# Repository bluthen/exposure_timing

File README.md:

# Exposure Timing

A lot of this project is based off New EXposure Timing Analyser (NEXTA): a GNSS-based precise timer, as presented in the wonderful paper [Reaching sub-millisecond accuracy in stellar
occultations and artificial satellites tracking](https://arxiv.org/abs/2301.06378)[arvix] ([local mirror](./nexta_2301.06378.pdf)) by authors K. Kamiński , C. Weber , A. Marciniak , M. Żołnowski & M. Gędek.

The goals are to design electronics and boards to make this easy to use.

 * PCBs that can be easily assembled, and manufactured that allow for easy LED bar registration (By having Aruco markers for example).
   * This should also make it easy to sell kits for people who do not want to solder or hand wire their own.
 * Software:
   * Binaries available for common desktop OS
   * Can automatically finds LED bar
   * Allow manually register LED bar
   * Decode each rows time
   * Generates timing info, real first exposure time, and time for any row (if rolling shutter camera). Recommends offset to be added to header/metadata. 

*Showing the simple GUI after time analysis has been run. Header delta is what should be added to the time stamp to make it more accurate.*

# License
Please note that individual files in the repository have different licenses. For example the NEXTA microcontroller code is under CC BY-SA 4.0 and the some of the analysis software is under the GNU GPL 3.

# Brief Description

There can be delays, or accuracy issues between when the camera is told to start it's exposure and when it actually does. This can be important for time critical applications. Also of importance is the time difference for each row in CMOS cameras with a rolling shutter.

In particular the timing application originally of interest is imaging fast time critical astronomical events. Such events include, LEO satilite, astroid transits, fast NEOs.

A better introduction is described in the paper listed above.

## Example usage

* Take your camera with a lens on it
* Put electronics (NEXTA) in front of camera, square, well focused.
* Take a intial well lit exposure used for LED bar registartion.
* After NEXTA gets GNSS lock and starts blinking, take short exposures in a dark area.
* Use analysis software to get timing info to see the difference between what is in header/metadata.

# Project contents

* [hardware](./hardware) - This includes 3d printed mount, PCB design files, and arduino firmware
* [nexta_analysis](./nexta_analysis) - Software to try to automatically decode timing images
* [nexta_html_decode_form](./nexta_html_decode_form) - A simple web form to decode the LED pattern into a time.

# Issues

There is a still a lot to do, this project is in it's early stages. Check out the [issue tracker](./issues) and, feel free to contribute.

# Instructional Videos/Purchase complete NEXTA kits

* [https://starsynctrackers.com/store/learn-nexta/](https://starsynctrackers.com/store/learn-nexta/) - Includes Arduino, assembled NEXTA Shield, GPS Moudle, GPS Antenna, Plastic Stand, and Micro USB Cable

# Other Projects

If you are interested in this project, you may be also interested in the following.

* [Project Pluto GNSS astrometry](https://www.projectpluto.com/gps_ast.htm) - Take GNSS satelites going across your frame. Since these positions are well known you can use this to get better timing (Probably up to 0.01s)

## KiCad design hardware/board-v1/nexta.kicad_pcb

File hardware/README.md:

# Exposure Timing Hardware

The goal here is to design PCB and other hardware to make registration and alignment easier for automatic timing analysis.

So far we have:
 * Schematics and PCB design ([KiCad](https://www.kicad.org/) and Gerbers)
 * 3d printed electronics stand ([FreeCad](https://www.freecad.org/) and STL)
 * The firmware (Arduino Sketch) provided by the authors of [Reaching sub-millisecond accuracy in stellar
   occultations and artificial satellites tracking](https://arxiv.org/abs/2301.06378)[arvix] ([local mirror](./nexta_2301.06378.pdf)) by authors K. Kamiński1 , C. Weber2 , A. Marciniak1 , M. Żołnowski3 & M. Gędek.

See the issue tracker for more work to be done.

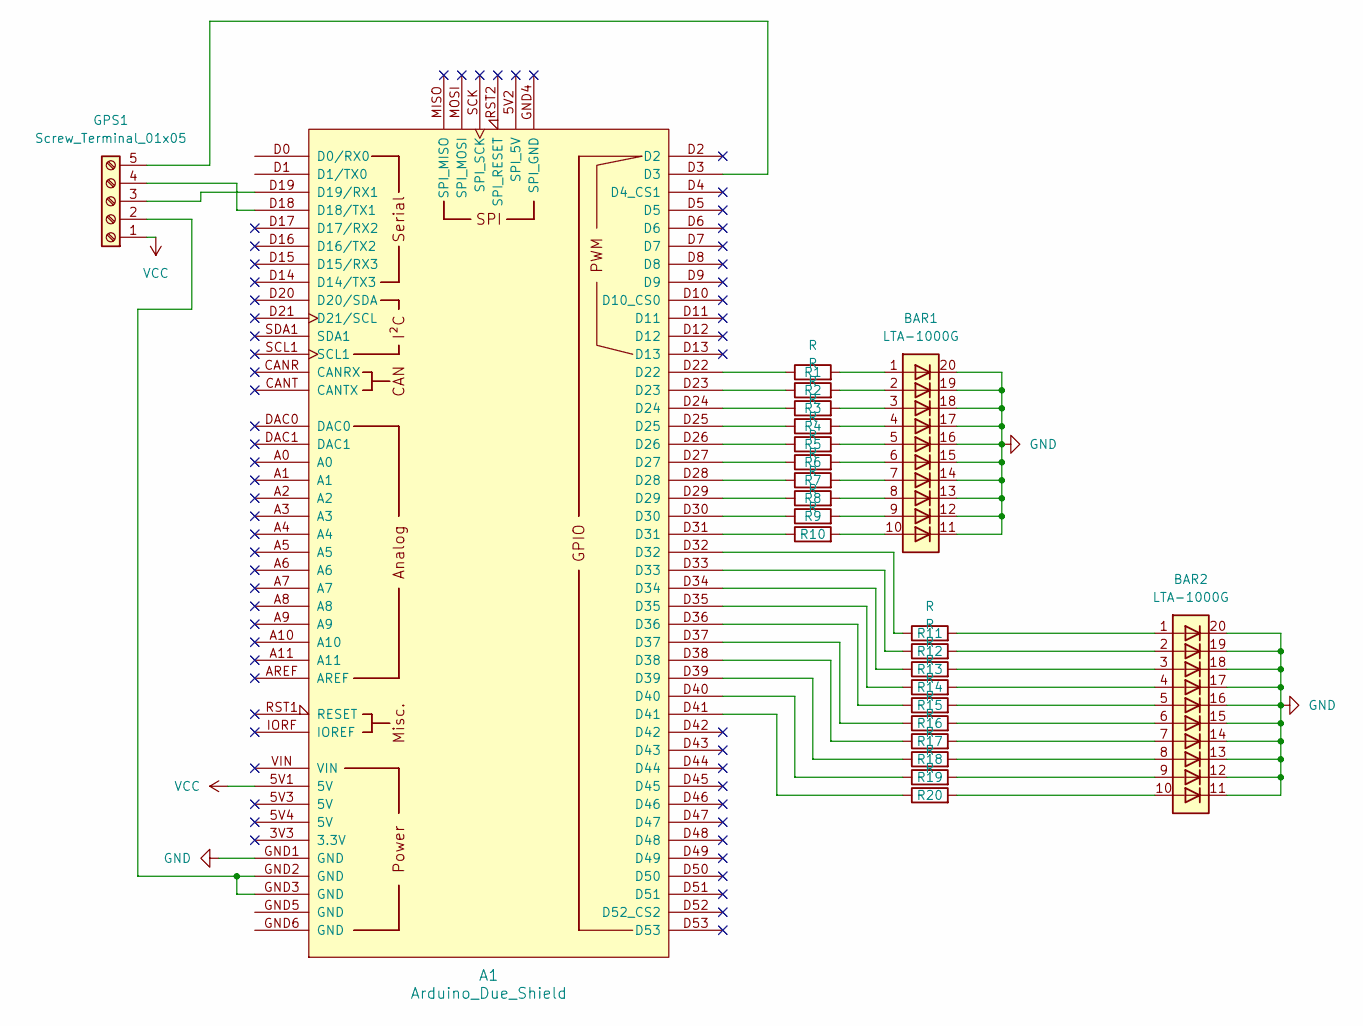
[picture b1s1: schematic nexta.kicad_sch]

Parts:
A1: Arduino_Due_Shield
BAR1, BAR2: LTA-1000G; HDSP-4850
GPS1: Screw_Terminal_01x05; PinHeader_1x05_P2.54mm_Vertical
R1, R2, R3, R4, R5, R6, R7, R8, R9, R10, R11, R12, R13, R14, R15, R16, R17, R18, R19, R20: R; R_0805_2012Metric

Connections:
GND: A1.GND1 (GND), BAR1.11 (K), BAR1.12 (K), BAR1.13 (K), BAR1.14 (K), BAR1.15 (K), BAR1.16 (K), BAR1.17 (K), BAR1.18 (K), BAR1.19 (K), BAR1.20 (K), BAR2.11 (K), BAR2.12 (K), BAR2.13 (K), BAR2.14 (K), BAR2.15 (K), BAR2.16 (K), BAR2.17 (K), BAR2.18 (K), BAR2.19 (K), BAR2.20 (K)
unnamed: A1.D18 (D18/TX1), GPS1.4
unnamed: A1.D19 (D19/RX1), GPS1.3
unnamed: A1.D22, R1.1
unnamed: A1.D23, R2.1
unnamed: A1.D24, R3.1
unnamed: A1.D25, R4.1
unnamed: A1.D26, R5.1
unnamed: A1.D27, R6.1
unnamed: A1.D28, R7.1
unnamed: A1.D29, R8.1
unnamed: A1.D30, R9.1
unnamed: A1.D31, R10.1
unnamed: A1.D32, R11.1
unnamed: A1.D33, R12.1
unnamed: A1.D34, R13.1
unnamed: A1.D35, R14.1
unnamed: A1.D36, R15.1
unnamed: A1.D37, R16.1
unnamed: A1.D38, R17.1
unnamed: A1.D39, R18.1
unnamed: A1.D40, R19.1
unnamed: A1.D41, R20.1
unnamed: BAR1.1 (A), R1.2
unnamed: BAR1.2 (A), R2.2
unnamed: BAR1.3 (A), R3.2
unnamed: BAR1.4 (A), R4.2
unnamed: BAR1.5 (A), R5.2
unnamed: BAR1.6 (A), R6.2
unnamed: BAR1.7 (A), R7.2
unnamed: BAR1.8 (A), R8.2
unnamed: BAR1.9 (A), R9.2
unnamed: BAR1.10 (A), R10.2
unnamed: BAR2.1 (A), R11.2
unnamed: BAR2.2 (A), R12.2
unnamed: BAR2.3 (A), R13.2
unnamed: BAR2.4 (A), R14.2
unnamed: BAR2.5 (A), R15.2
unnamed: BAR2.6 (A), R16.2
unnamed: BAR2.7 (A), R17.2
unnamed: BAR2.8 (A), R18.2
unnamed: BAR2.9 (A), R19.2
unnamed: BAR2.10 (A), R20.2
unnamed: A1.GND2 (GND), A1.GND3 (GND), GPS1.2
unnamed: A1.D3, GPS1.5
VCC: A1.5V1 (5V), GPS1.1

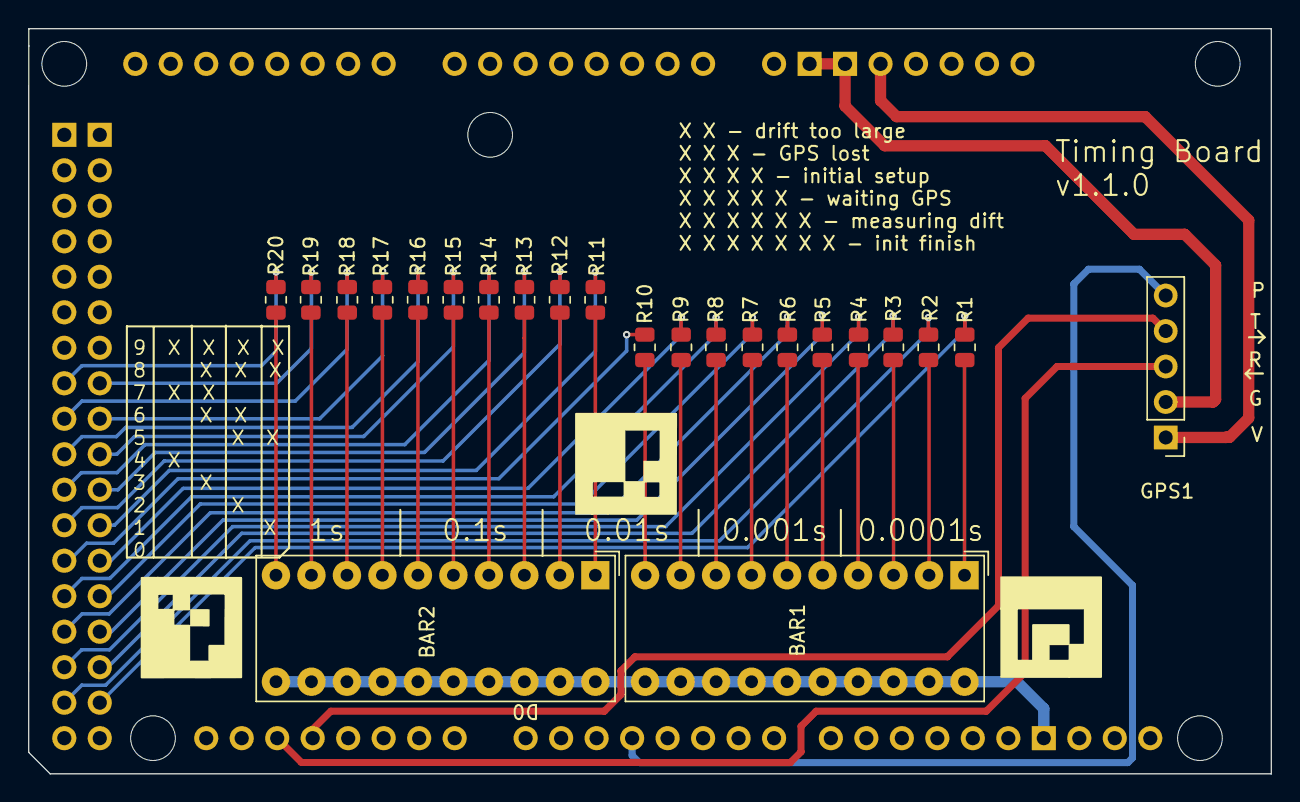
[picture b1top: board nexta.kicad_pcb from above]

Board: 2 copper layers, 88.9 x 53.3 mm, 24 parts (0 on the bottom side), 46 nets.

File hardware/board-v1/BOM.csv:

Designation,Part,Link
"R1,R2,R3,R3,R5,R6,R7,R8,R9,R10,R11,R12,R13,R14,R15,R16,R17,R18,R19,R20",0805 1k Ohm Resistor,https://www.digikey.com/en/products/detail/walsin-technology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
"BAR1,BAR2",LTA-1000G,https://www.digikey.com/en/products/detail/liteon/LTA-1000G/153278
GPS1,UBLOX NEO-7M Module,https://www.ebay.com/sch/i.html?_from=R40&_trksid=p4432023.m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
Arduino Due,,https://www.digikey.com/en/products/detail/arduino/A000062/3712582
,Male .1” headers,https://www.digikey.com/en/products/detail/4-103327-0/A26514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

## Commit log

2024-01-16 Initial commit.
2024-01-16 Added GPS antenna to bom.
2024-01-16 Fixed a type-o
2024-01-16 Improved rolling shutter calculation using 1ms led vertical patterns.
2024-01-17 Updated globber for new stats json format.
2024-01-20 4 Aruco markers, and faceplate.
2024-01-20 rename folder board-v1 to pcb
2024-01-20 Added M3 8mm standoff for faceplate.
2024-01-22 Improved performance on my machine from 60 seconds to 1.3s
2024-01-23 Works with bayer, and 3 channel fits. Also uses exptime for best err.
2024-01-28 LED Selector has support for v2 boards.
2024-02-07 Added a simple GUI in tkinter.
2024-02-11 Able to do manual registration in app with tk widget instead of opencv imshow.
2024-02-12 Uses debug_show instead of cv2.imshow for displaying debug images.
2024-02-12 read_time_gui can run headless registration or readtime from commandline args.
2024-02-12 import cleanup
2024-02-12 Seting up for pyinstaller github action.
2024-02-12 action "3.10" python
2024-02-12 update pip comment in action.
2024-02-13 Update file names in github action.
2024-02-13 A little better about clearing registration.
2024-02-13 Updated readme for show the GUI.
2024-02-13 Try 3.11.1 in python action.
2024-02-13 Update python version to make get a universal2 build.
2024-02-13 Remove reference numbers after author names from copy/paste error.
2024-02-13 Try again for universal2 build.
2024-02-13 Try archs
2024-02-13 just x86_64 builds for now.
2024-03-09 For a rolling shutter type, try to use latest incremented row for basetime.
2024-03-24 GPS Baud 56700, correct_drift uncommented.
2024-03-24 Added LED-on iterate at very beginning just to check wiring.
2024-04-01 Slight adjustment to threshold for finding leds areas. Very basic help and about added to gui.
2024-04-01 Fixed action menu.
2024-04-01 Version bump of nexta analysis.
2024-04-01 PCB 2.1.0
2024-04-01 Fixed image link.
2024-05-08 Include link to buy pre assembled kits.
2024-05-08 Cleanup
2024-05-08 / instead of , in readme.
2025-02-02 NEXTA Enclosure created by Vadim Nikitin.
